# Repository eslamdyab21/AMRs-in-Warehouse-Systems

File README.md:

# AMRs-in-Warehouse-Systems
This repository is for our graduation project ‫‪AMRs‬‬ ‫‪in‬‬ ‫‪Warehouse‬‬ ‫‪Systems, A team in the Faculty of Engineering, Alexandria university, majored in Electronics and Communication.

The repository have 5 main branches, main, software, embedded, data and devops. each branch has its corresponding tasks represented in issues.

Inside the `docs` folder there is a documentation for each issue documenting producers taken to solve the issue. 

Our team uses **Obsidian** for documentation and here is an image from the program visualizing each issue/task as a node and its connection to other nodes.

<br/>

## System overview 

Our project tackles a full end-to-end system to operates a warehouse starting from the client side to monitoring the warehouse at the admin side. A warehouse stores a number of packages which is stored inside different shelves, and robots move those shelves autonomously -when an order is made- from point A to B -their current location to the packaging location-. 

To do so, the system was divided into the above parts: 
- Customers website: for customers to access packages and make orders.

- Admin website: for admins to monitor the system in case any problems occurred, developed in react and javascript and apis between the backend and frotend.
<br/>

- Database: to store the warehouse (robots, shelves, packages, ....) different information and customers data, we used postgres.
<br/>

- Cloud and Devops: to create the infrastructure on which the websites and database will work, we used AWS, Jenkins and Circle-Ci.
<br/>

- Algorithm: to control the robots movements inside the warehouse, shortest and free of obstacles path for each robot to minimize time and battery usage and avoid collisions, ad communication between different parts and different robots in the algorithm is done in ROS.
<br/>

- Embedded: the layer which will actually move the robots in the hardware sense, with different sensors, raspberry pi and digital cameras, and developed in ARM.
<br/>

The development of the system was inspired by the **micro services** design so that each part does a specific task and its failure doesn't directly affect the whole system. 

Also some of the system components are **deodorized** so that the system can run on any machine with any os without compatibility issues with one command.

<br/>

## Robot design and demo

[Demo Video](https://youtu.be/BpZr7LPZxno)

<br/>

## How to run the system locally
For the admin website and the database, the easiest way is to install their docker images from dockerhub and run them with the following commands.

First make the system docker network on which the containers will communicate 
```bash
docker network create warehouse-network
```

<br/>

- For the database
```bash
docker run --name dashboard-database -v database-volume:/shared-volume --network warehouse-network -p 5432:5432 -d eslamdyba/amrs-in-warehouse-systems:dashboard-database-postgres-1.0
```
This command will install the system database docker image, make a container named `dashboard-database` and attach it a volume so data is preserved, and will run it on port 5432.

The database will be empty in a fresh install, you can add initial data with the following:
1. enter the database docker container, this will give you the container shell.
```bash
docker exec -it dashboard-database sh
```

2. login to the database
```bash
psql -h host_name -p port_number -U user_name -d database_name
```

- In our case
```bash
psql -h localhost -p 5432 -U postgres -d AMR_Warehouse
```

3. enter sql commands to insert some data
```bash
INSERT INTO Customers VALUES('C1', 'menna@gmail', 'mennapassword', 'Mennatallah Mamdouh', 'Female');

INSERT INTO Products VALUES('P1', 'Hair Shampoo', 250, 'It is a hair product. It contains Sulfates', 500, 'URL1', 'URL2', 'URL3'),
                            ('P2', 'Hair Conditioner', 300, 'It is a hair product. It controls frizzness', 500, 'URL1', 'URL2', 'URL3');

INSERT INTO Shelves(ShelfID, Location_X, Location_Y, ProductID, NumOfOrders)
VALUES('S1', 0, 5, 'P1', 0), ('S2', 0, 10, 'P2', 0);

INSERT INTO Orders_Details VALUES('O1', 'C1', NULL, NOW(), '+201234567890', 'Alexandria', 'Cash on Delivery', 'New'),
                                    ('O2', 'C1', NULL, NOW(), '+201234567890', 'Alexandria', 'Cash on Delivery', 'New');

INSERT INTO Orders(OrderID, ProductID, Quantity) VALUES('O1', 'P1', 5), ('O1', 'P2', 7), ('O2', 'P1', 7);

INSERT INTO Robots(RobotID, Speed, BatteryPercentage, CurrentLocation_X, CurrentLocation_Y, isCharging, ShelfID)
VALUES('R1', 90, 100, 5, 5, False, 'S1'), ('R2', 80, 50, 10, 10, False, 'S2');
```

<br/>

- For the admin website backend
```bash
docker run --name dashboard-backend -p 5000:5000 --network warehouse-network -d eslamdyba/amrs-in-warehouse-systems:dashboard-backend-1.0
```
This command will install the system admin website backend docker image, make a container named `dashboard-backend` and will run it on port 5000.

<br/>

- For the admin website frontend
```bash
docker run --name dashboard-frontend -p 3001:3000 --network warehouse-network -d eslamdyba/amrs-in-warehouse-systems:dashboard-frontend-1.0

```
This command will install the system admin website frontend docker image, make a container named `dashboard-frontend` and will run it on port 3001. You should see the website running when entering the URL `localhost:3000` on your browser.

<br/>

Now you should see the container running when `docker ps`

you can either install ROS dirctly on your machine, or download its docker image from dockerhub.

Then for the algorithm you can follow the above overview video which explains the different parts of the system and how to run it both as a simulation and hardware.

<br/>

You can find more information and explanation in the `docs` folder.

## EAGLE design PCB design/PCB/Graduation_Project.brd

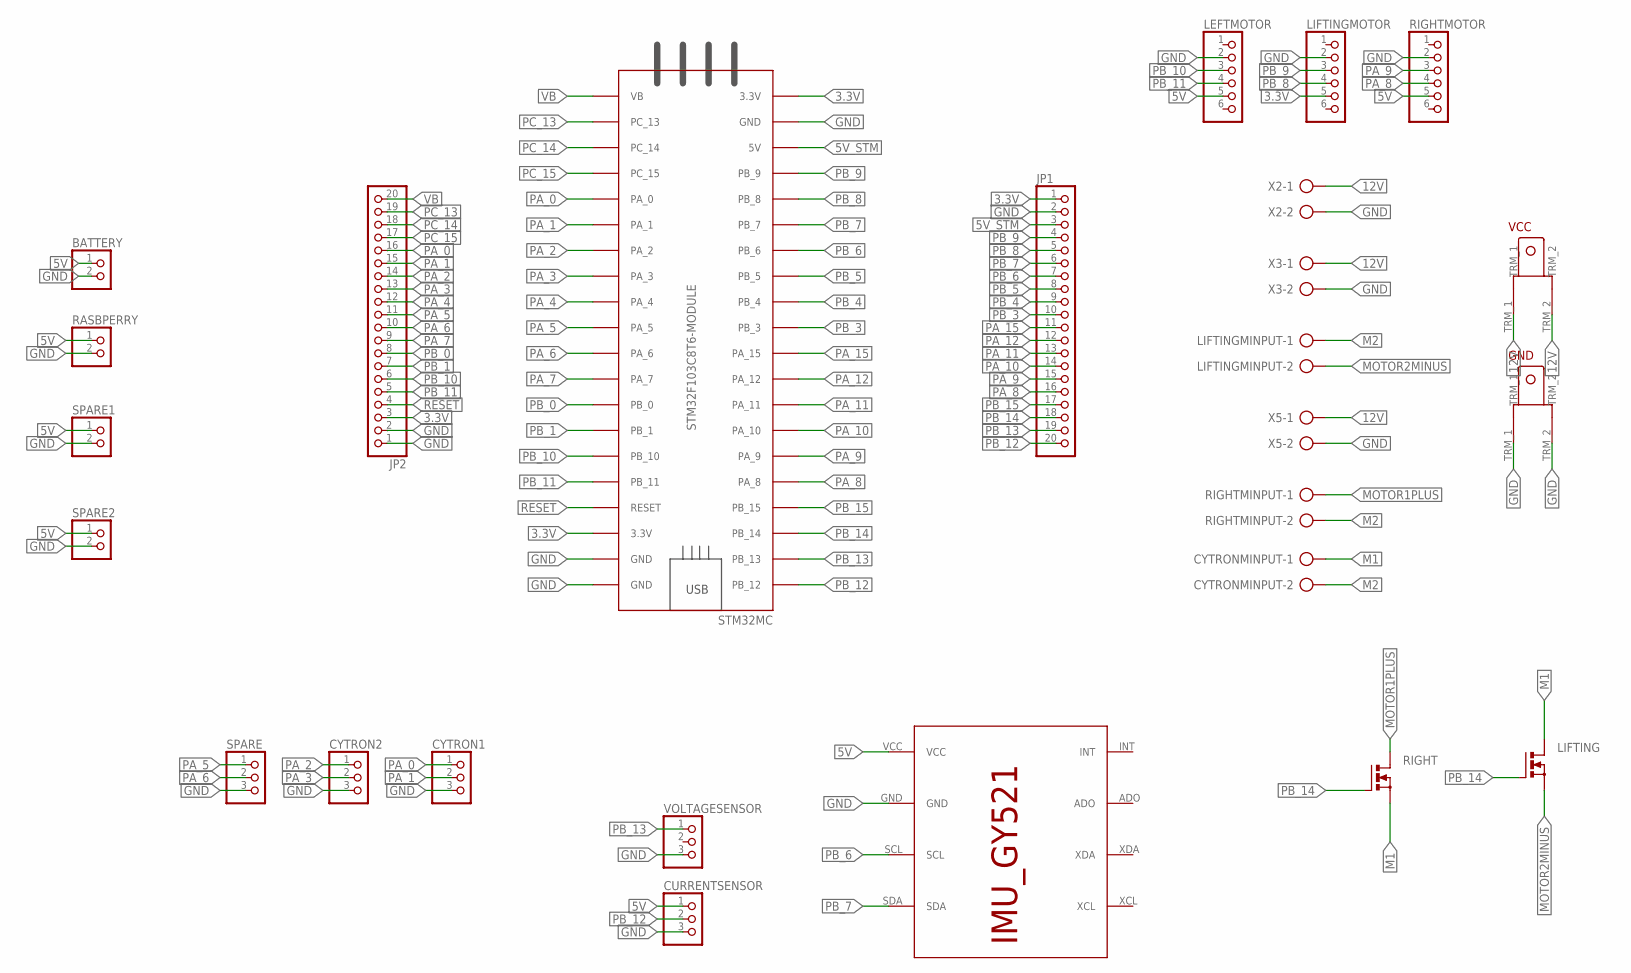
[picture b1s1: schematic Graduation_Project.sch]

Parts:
BATTERY: PINHD-1X2; 1X02
CURRENTSENSOR: PINHD-1X3; 1X03
CYTRON1, CYTRON2: PINHD-1X3; 1X03
CYTRONMINPUT: AK300/2
GND: TERMINAL_EDITED
JP1, JP2: PINHD-1X20; 1X20
LEFTMOTOR: PINHD-1X6; 1X06
LIFTING: MOSFET_NTO220BH; TO220BH
LIFTINGMINPUT: AK300/2
LIFTINGMOTOR: PINHD-1X6; 1X06
RASBPERRY: PINHD-1X2; 1X02
RIGHT: MOSFET_NTO220BH; TO220BH
RIGHTMINPUT: AK300/2
RIGHTMOTOR: PINHD-1X6; 1X06
SPARE: PINHD-1X3; 1X03
SPARE1, SPARE2: PINHD-1X2; 1X02
STM32MC: STM32F103C8T6-MODULE
U$1: IMU_ROBOCON_GY521; IMU_GY521
VCC: TERMINAL_EDITED
VOLTAGESENSOR: PINHD-1X3; 1X03
X2, X3, X5: AK300/2

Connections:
3.3V: JP1.1, JP2.3, LIFTINGMOTOR.5, STM32MC.3.3V_1 (3.3V), STM32MC.3.3V_2 (3.3V)
5V: BATTERY.1, CURRENTSENSOR.1, LEFTMOTOR.5, RASBPERRY.1, RIGHTMOTOR.5, SPARE1.1, SPARE2.1, U$1.VCC
5V_STM: JP1.3, STM32MC.5V
12V: VCC.TRM_1, VCC.TRM_2, X2.1, X3.1, X5.1
GND: BATTERY.2, CURRENTSENSOR.3, CYTRON1.3, CYTRON2.3, GND.TRM_1, GND.TRM_2, JP1.2, JP2.1, JP2.2, LEFTMOTOR.2, LIFTINGMOTOR.2, RASBPERRY.2, RIGHTMOTOR.2, SPARE.3, SPARE1.2, SPARE2.2, STM32MC.GND_1 (GND), STM32MC.GND_2 (GND), STM32MC.GND_3 (GND), U$1.GND, VOLTAGESENSOR.3, X2.2, X3.2, X5.2
M1: CYTRONMINPUT.1, LIFTING.D, RIGHT.S
M2: CYTRONMINPUT.2, LIFTINGMINPUT.1, RIGHTMINPUT.2
MOTOR1PLUS: RIGHT.D, RIGHTMINPUT.1
MOTOR2MINUS: LIFTING.S, LIFTINGMINPUT.2
PA_0: CYTRON1.1, JP2.16, STM32MC.PA_0
PA_1: CYTRON1.2, JP2.15, STM32MC.PA_1
PA_2: CYTRON2.1, JP2.14, STM32MC.PA_2
PA_3: CYTRON2.2, JP2.13, STM32MC.PA_3
PA_4: JP2.12, STM32MC.PA_4
PA_5: JP2.11, SPARE.1, STM32MC.PA_5
PA_6: JP2.10, SPARE.2, STM32MC.PA_6
PA_7: JP2.9, STM32MC.PA_7
PA_8: JP1.16, RIGHTMOTOR.4, STM32MC.PA_8
PA_9: JP1.15, RIGHTMOTOR.3, STM32MC.PA_9
PA_10: JP1.14, STM32MC.PA_10
PA_11: JP1.13, STM32MC.PA_11
PA_12: JP1.12, STM32MC.PA_12
PA_15: JP1.11, STM32MC.PA_15
PB_0: JP2.8, STM32MC.PB_0
PB_1: JP2.7, STM32MC.PB_1
PB_3: JP1.10, STM32MC.PB_3
PB_4: JP1.9, STM32MC.PB_4
PB_5: JP1.8, STM32MC.PB_5
PB_6: JP1.7, STM32MC.PB_6, U$1.SCL
PB_7: JP1.6, STM32MC.PB_7, U$1.SDA
PB_8: JP1.5, LIFTINGMOTOR.4, STM32MC.PB_8
PB_9: JP1.4, LIFTINGMOTOR.3, STM32MC.PB_9
PB_10: JP2.6, LEFTMOTOR.3, STM32MC.PB_10
PB_11: JP2.5, LEFTMOTOR.4, STM32MC.PB_11
PB_12: CURRENTSENSOR.2, JP1.20, STM32MC.PB_12
PB_13: JP1.19, STM32MC.PB_13, VOLTAGESENSOR.1
PB_14: JP1.18, LIFTING.G, RIGHT.G, STM32MC.PB_14
PB_15: JP1.17, STM32MC.PB_15
PC_13: JP2.19, STM32MC.PC_13
PC_14: JP2.18, STM32MC.PC_14
PC_15: JP2.17, STM32MC.PC_15
RESET: JP2.4, STM32MC.RESET
VB: JP2.20, STM32MC.VB

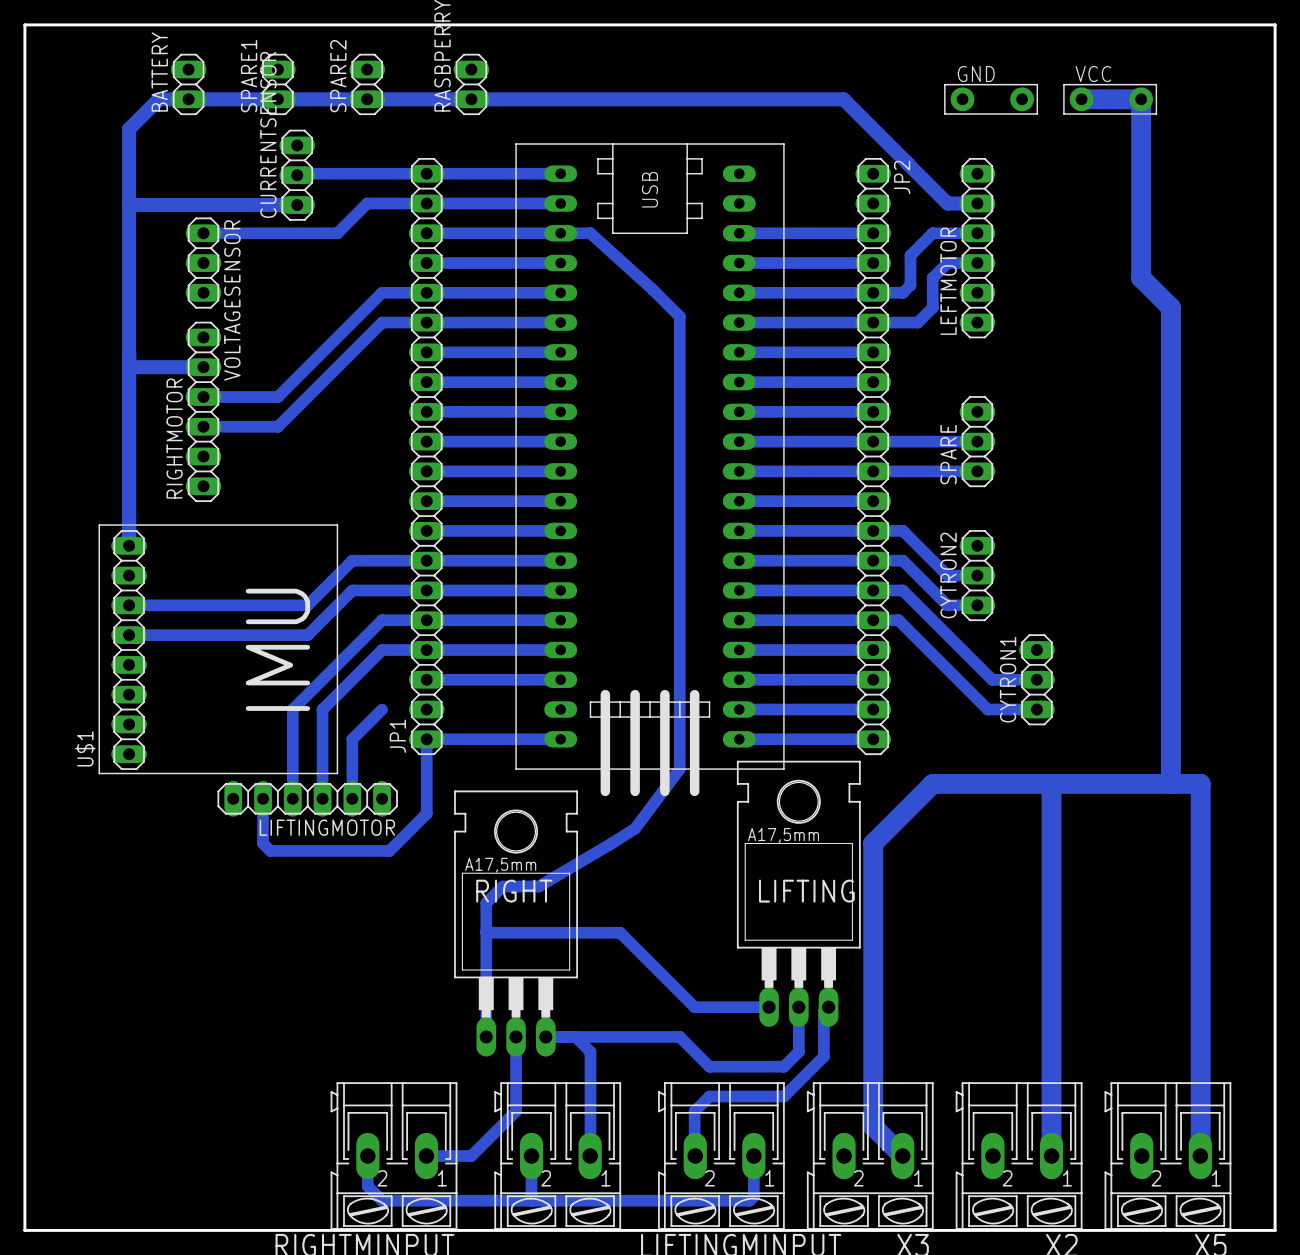
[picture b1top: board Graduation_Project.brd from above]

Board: 2 copper layers, 106.7 x 102.9 mm, 26 parts (0 on the bottom side), 43 nets.

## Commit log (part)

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2023-04-25 added commands for connecting and disconnecting to a database -fixes #36
2023-04-25 added a notebook contains the evaluation of the servers -fixes #36
2023-04-25 made random data instead of inserting or updating the same data every time to avoid caching -fixes #36
2023-04-25 increased the sample size with 200 instead of 90 to get more accurate results -fixes #36
2023-04-25 edited a typo in the notebook -fixes #36
2023-04-25 added issue number to the name of the documentation file database-servers -fixes #36
2023-04-25 edited the gitignore file -fixes #36
2023-04-25 edited the documentation of this issue to contain the details of the experiment -fixes #36
2023-04-25 added the images in the documentation file -fixes #36
2023-04-25 added a notebook which contains some analysis of the servers performance results -fixes #36
2023-04-25 edited some graphs in the analysis notebook -fixes #36
2023-04-25 added the images of the plots -fixes #36
2023-04-25 added the analysis part to the documentation file -fixes #36
2023-04-25 deleted the old database creation file -fixes #23
2023-04-25 added a new file contains the database tables only -fixes #23
2023-04-25 added some notes -fixes #23
2023-04-25 switched the Orders table and the Orders_Details table as well as their relationship -fixes #23
2023-04-25 added the database code written in PostgreSQL Server -fixes #23
2023-04-25 switched the names of Orders and Orderd_Details tables to be more descriptive -fixes #23
2023-04-25 added a new trigger to check the products items in stock -fixes #23
2023-04-25 edited the postgres features file -fixes #23
2023-04-25 renamed the original database files with mysql -fixes #23
2023-04-25 add ros to control and make it for one robot - fixes #53
2023-04-25 update gitignore - fixes #53
2023-04-25 comment prints - fixes #53
2023-04-25 loop in main - fixes #53
2023-04-25 Create PCB Fabrication
    Steps to make PCB HW - fixes #16
2023-04-25 Rename Readme to ReadME.md
2023-04-25 Update ReadME.md
    Issue#16 Documentation
2023-04-25 edited the trigger NotifyMe in the database features -fixes #23
2023-04-25 deleted the testing database -fixes #23
2023-04-25 edited the triggers in MySQL database -fixes #23
2023-04-25 fix ros subscrips error with astar map - fixes #53
2023-04-25 edited some tables in the database -fixes #23
2023-04-25 edited in the testing-queries file -fixes #23
2023-04-26 added some test queries -fixes #23
2023-04-26 added the view to the features file -fixes #23
2023-04-26 added the images of the tables after normalization -fixes #47
2023-04-26 edited the documentation file of the data normalization issue -fixes #47
2023-04-26 added a readme file to the data normalization folder -fixes #47
2023-04-26 change columns names for new postgres db - fixes #5
2023-04-26 allow frontend to access db and send only table rows from backend - fixes #5
2023-04-26 Update ReadME.md
    Correct the mistakes on the readme file
2023-04-26 Deleted' Arduino Encoders code @12.md' as it doesn't match any issue name and resolves conflict with every merge - fixes #7
2023-04-26 Added Documentation of the issue - fixes #7
2023-04-26 Changed the images size - fixes #7
2023-04-26 added the new ERD (image and drawing file) -fixes #23
2023-04-26 edited the testing queries to be inserted in order -fixes #23
2023-04-26 removed the mysql database codes -fixes #23
2023-04-26 edited the image of ERD in the documentation -fixes #23
2023-04-26 edited the documentation and the README file of this issue -fixes #23
2023-04-26 edited the headlines of the documentation -fixes #23
2023-04-26 added a table of contents to the README file -fixes #23
2023-04-27 add postgres-database-tables.sql from database-creation - fixes #48
2023-04-27 add main script for testing pdate speed - fixes #48
2023-04-27 update docs - fixes #48
2023-04-27 add logging info for comparsion between docker container and host - fixes #48
2023-04-27 add docs images folder for data- fixes #48
2023-04-27 fix image format in docs - fixes #48
2023-04-28 Returned the files with problems of merging
2023-04-28 adjust main to take a paramter for robot number - fixes #53
2023-04-28 add logger in ros callback, and adjust steps_map - fixes #48
2023-04-28 Update ReadME.md
    Updating readme file
2023-04-29 added ADC driver - fixes #35
2023-04-29 renamed folder - fixes #35
2023-04-29 added README file - fixes #35
2023-04-29 added the documentation - fixes #33
2023-04-29 added README file - fixes #33
2023-04-30 Added PID constants topic and declarations - fixes #17
2023-05-01 add a movement status topic for master ro handle assignning robots with orders - fixes #53
2023-05-01 change master name class and add topic to track robots movment status to assign shelves to them - fixes #53
2023-05-02 rename Control class to Robot_Control - fixes #53
2023-05-03 added the products data on the website -fixes #23
2023-05-03 connected the user-login page to the database -fixes #6
2023-05-03 connected the home page to the database -fixes #6
2023-05-03 connected the wishlist page and the wishlist-cart component to the database -fixes #6
2023-05-03 connected the shop page to the database -fixes #6
2023-05-04 connected the update-user page to the database -fixes #6
2023-05-04 added a table (Cart) to store the products in each customer's cart during shopping -fixes #23
2023-05-04 optimized some queries in the wishlist component -fixes #6
2023-05-04 connected the category page to the database -fixes #6
2023-05-04 edited the connect file to contain the information of the connection as environment variables -fixes #6
2023-05-04 added the .env file of the website to gitignore -fixes #6
2023-05-04 connected the cart page to the database -fixes #6
2023-05-04 updated the max quantity in the search page to be equal the items in stock -fixes #6
2023-05-04 edited the customerid part in the user_register code -fixes #6
2023-05-05 connected the orders page to the database -fixes #6
2023-05-05 edited the message_id part in the contact code -fixes #6
2023-05-07 added the documentation of the back-end database link of the website -fixes #73
2023-05-07 added a table of contents to this issue's doc -fixes #73
2023-05-07 edited the table of contents of this issue -fixes #73
2023-05-09 get min cost robot and assign it to robot node - fixes #53
2023-05-09 rename topics and subscripe from master - fixes #53
2023-05-28 moved .circleci
2023-05-28 fix indentation error - fixes #5
2023-05-28 we fixed the directory error - fixes #5
2023-05-28 comment the build in backend - fixes #5
2023-05-29 wait for stom to responde in motion - fixes #53
2023-06-04 add jenkins files for ci pipline -fixes #5
2023-06-05 move jenkins files -fixes #5
2023-06-05 typo -fixes #5
2023-06-05 edit jenkins files to find packages.json -fixes #5
2023-06-05 create a dockerfile for frontend image -fixes #5
2023-06-05 edit typo -fixes #5
2023-06-05 add serve module with dependencies -fixes #5
2023-06-05 change docker last cmd -fixes #5
2023-06-07 change port number and node version to fix serve error -fixes #5
2023-06-10 Updated movement function to handle +ve and -ve also updated pub - fixes #17
2023-06-13 change varables names in side-bar - fixes #5
2023-06-13 upgrade app version number for dockerhub - fixes #5
2023-06-13 change admin photo - fixes #5
2023-06-14 add jenkins pipelines and setup notes - fixes #74
2023-06-14 rename devops folder - fixes #74
2023-06-14 add .obsidian to gitignore - fixes #74
2023-06-24 added the username and database name arguments to the docker file -fixes #48
2023-06-24 added the features file of the database -fixes #48
2023-06-24 added a command to copy the features file to the container -fixes #48
2023-06-24 renamed the database file -fixes #48
2023-06-24 update databse for postgress with ros - fixes #53
2023-06-24 rename Master_db to two nodes one for querying and one for updating with ros - fixes #53
2023-06-24 handle env variables outside of env file - fixes #75
2023-06-24 add Jenkinsfile for ci pipline - fixes #75
2023-06-24 add scripts.groovy for ci pipline - fixes #75
2023-06-25 update build stage to take env varibles needed for the backend - fixes #75
2023-06-25 fix updationg db, null problem - fixes #53
2023-06-25 added a new field in the orders table to get the status for each order-product pair -fixes #23
2023-06-25 added 2 new triggers, one for checking the order status and the second is for monitoring the shelves paired with robots and their orders -fixes #23
2023-06-25 add pipeline for creating and pushing the docker image for the database server -fixes #48
2023-06-25 edited the path of the docker file -fixes #48
2023-06-25 edited the path of the database file in the docker file -fixes #48
2023-06-25 add control to when a shelf is connected to robot - fixes #53
2023-06-25 querey only the shelf who is not paired with a robot - fixes #53
2023-06-25 make paried-with-shelf default value null- fixes #53
2023-06-26 added system code - fixes #14
2023-06-26 added a new feature to view summary data on the dashboard of the web-application -fixes #23
2023-06-26 edited the admin_view and added more information in it -fixes #23
2023-06-26 added a new feature to view the statistical summary in the web application dashboard main page -fixes #48
2023-06-27 add map2d for backend -fixes #5
2023-06-27 fix db name in backend -fixes #5
2023-06-28 added cubeIDE code - fixes #14
2023-06-28 add graphs to pages - fixes #5
2023-06-29 fix errors in updating db - fixes #53
2023-06-29 fix updating db shelf name issue and update shelves locations also - fixes #53
2023-06-29 handle if shelf and robot are in the same postion -fixes #5
2023-06-30 control robot manauly wsda - fixes #53
2023-07-01 add c char to exit program - fixes #53
2023-07-01 increase warehouse map to 15x15
2023-07-01 Final arduino code with pid testing and debugging - fixes #17
2023-07-01 Python file for testing pid on the pi - fixes #17
2023-07-01 Python file for testing movement on the pi - fixes #17
2023-07-02 remove wornnings when build - fixes #5
2023-07-02 job of creating infrastructure -fixes #5
2023-07-02 fix typo and infrastructure template -fixes #5
2023-07-02 listen from any branch -fixes #5
2023-07-03 add inventory file -fixes #5
2023-07-03 test only create infrastructure -fixes #5
2023-07-04 add config infrastructure job -fixes #5
2023-07-04 added a documentation for the vieww -fixes #23
2023-07-04 run create infrastructure job -fixes #5
2023-07-04 added a .env file to gitignore -fixes #6
2023-07-04 run config infrastructure job -fixes #5
2023-07-04 added the changes in the tables and features of the database -fixes #6
2023-07-04 added the ecommece-website data -fixes #48
2023-07-04 added the data file to Dockerfile -fixes #48
2023-07-04 add deploy frontend job -fixes #5
2023-07-04 added runs to Dockerfile -fixes #48
2023-07-04 commented copying the data file -fixes #48
2023-07-04 remove file of frontend -fixes #5
2023-07-04 renamed the data file -fixes #48
2023-07-04 removed the RUN commands -fixes #48
2023-07-04 ls for files in roles -fixes #5
2023-07-04 get backend server ip again in the deploy-frontend job
2023-07-05 fix directory fixes #5
2023-07-05 fix ~ / to abs path fixes #5
2023-07-05 increasing size of instance and installing latesr version of node - fixes #5
2023-07-06 added communication part - fixes #14
2023-07-06 change flow from npm to docker -fixes #5
2023-07-07 deploy database - fixes #5
2023-07-08 consle log env vars of database - fixes #75
2023-07-08 add >> to save text in the .env.local file - fixes #5
2023-07-09 Update about.php for the Graduation Project Team -fixes #6
    all images are included in images folder
2023-07-09 smoke-test - fixes #5
2023-07-10 add map2d and orders quereies
2023-07-10 add PID - fixes #14
2023-08-06 remove unnessasry pages - fixes #5
2023-08-10 handle going to packaging area - fixes #53
2023-08-12 decrease battery life as robots move - fixes #53
2023-08-13 iitial warehouse system paramaters - fixes #53
2023-08-13 update gitignore
2023-09-19 avoid shelves when moving even if robot is not paired with any shelf, except the shelf it will pair with - fixes #53
